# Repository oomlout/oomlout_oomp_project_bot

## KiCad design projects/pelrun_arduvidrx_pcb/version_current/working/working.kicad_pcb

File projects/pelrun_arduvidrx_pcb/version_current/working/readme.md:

# OOMP Project  
## arduvidrx_pcb  by pelrun  
  
oomp key: oomp_projects_flat_pelrun_arduvidrx_pcb  
(snippet of original readme)  

  full source readme at [readme_src.md](readme_src.md)  
  
source repo at: [https://github.com/pelrun/arduvidrx_pcb](https://github.com/pelrun/arduvidrx_pcb)  
## Board  

## Schematic  

[schematic pdf](working_schematic.pdf)  
## Images

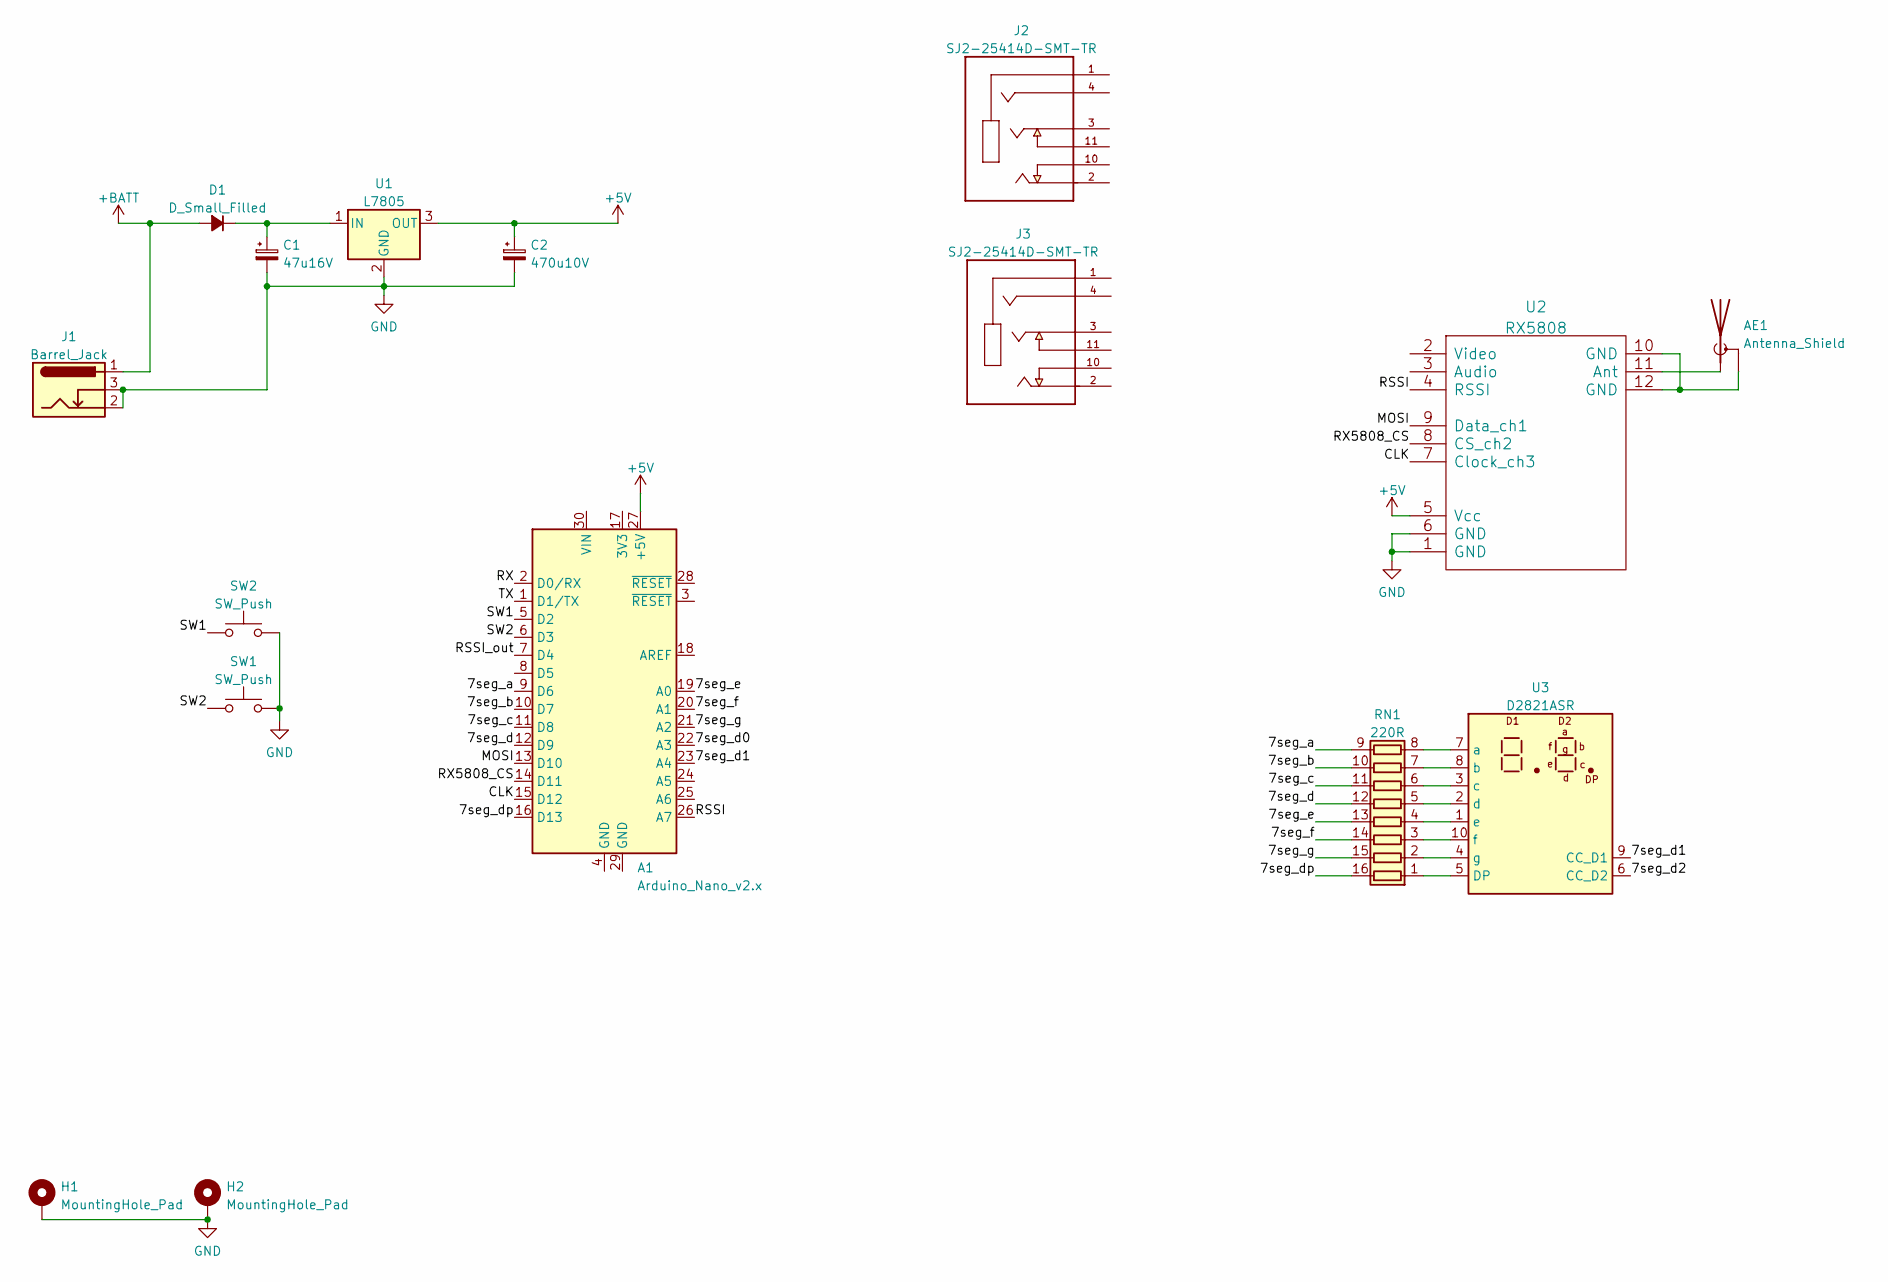
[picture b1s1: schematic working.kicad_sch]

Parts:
A1: Arduino_Nano_v2.x; Arduino_Nano
AE1: Antenna_Shield; SMA_Samtec_SMA-J-P-X-ST-EM1_EdgeMount
C1: 47u16V; CP_Radial_D4.0mm_P2.00mm
C2: 470u10V; CP_Radial_D4.0mm_P2.00mm
D1: D_Small_Filled; D_SMA-SMB_Universal_Handsoldering
H1, H2: MountingHole_Pad; MountingHole_3mm_Pad
J1: Barrel_Jack; PJ040CH
J2, J3: SJ2-25414D-SMT-TR; CUI_SJ2-25414D-SMT-TR; PARTREV 1.01
RN1: 220R; R_Array_Convex_8x0602
SW1, SW2: SW_Push; SW_PUSH_6mm_H13mm
U1: L7805; TO-252-2
U2: RX5808
U3: D2821ASR; HDSP-7401

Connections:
+5V: A1.27 (+5V), C2.1, U1.3 (OUT), U2.5 (Vcc)
+BATT: D1.2 (A), J1.1
/7seg_a: A1.9 (D6), RN1.9 (R8.2)
/7seg_b: A1.10 (D7), RN1.10 (R7.2)
/7seg_c: A1.11 (D8), RN1.11 (R6.2)
/7seg_d: A1.12 (D9), RN1.12 (R5.2)
/7seg_d0: A1.22 (A3)
/7seg_d1: A1.23 (A4), U3.9 (CC_D1)
/7seg_d2: U3.6 (CC_D2)
/7seg_dp: A1.16 (D13), RN1.16 (R1.2)
/7seg_e: A1.19 (A0), RN1.13 (R4.2)
/7seg_f: A1.20 (A1), RN1.14 (R3.2)
/7seg_g: A1.21 (A2), RN1.15 (R2.2)
/CLK: A1.15 (D12), U2.7 (Clock_ch3)
/MOSI: A1.13 (D10), U2.9 (Data_ch1)
/RSSI: A1.26 (A7), U2.4 (RSSI)
/RSSI_out: A1.7 (D4)
/RX: A1.2 (D0/RX)
/RX5808_CS: A1.14 (D11), U2.8 (CS_ch2)
/SW1: A1.5 (D2), SW2.1
/SW2: A1.6 (D3), SW1.1
/TX: A1.1 (D1/TX)
GND: C1.2, C2.2, H1.1, H2.1, J1.2, J1.3, SW1.2, SW2.2, U1.2 (GND), U2.1 (GND), U2.6 (GND)
unnamed: AE1.1 (A), U2.11 (Ant)
unnamed: AE1.2 (Shield), U2.10 (GND), U2.12 (GND)
unnamed: C1.1, D1.1 (K), U1.1 (IN)
unnamed: RN1.1 (R1.1), U3.5 (DP)
unnamed: RN1.2 (R2.1), U3.4 (g)
unnamed: RN1.3 (R3.1), U3.10 (f)
unnamed: RN1.4 (R4.1), U3.1 (e)
unnamed: RN1.5 (R5.1), U3.2 (d)
unnamed: RN1.6 (R6.1), U3.3 (c)
unnamed: RN1.7 (R7.1), U3.8 (b)
unnamed: RN1.8 (R8.1), U3.7 (a)

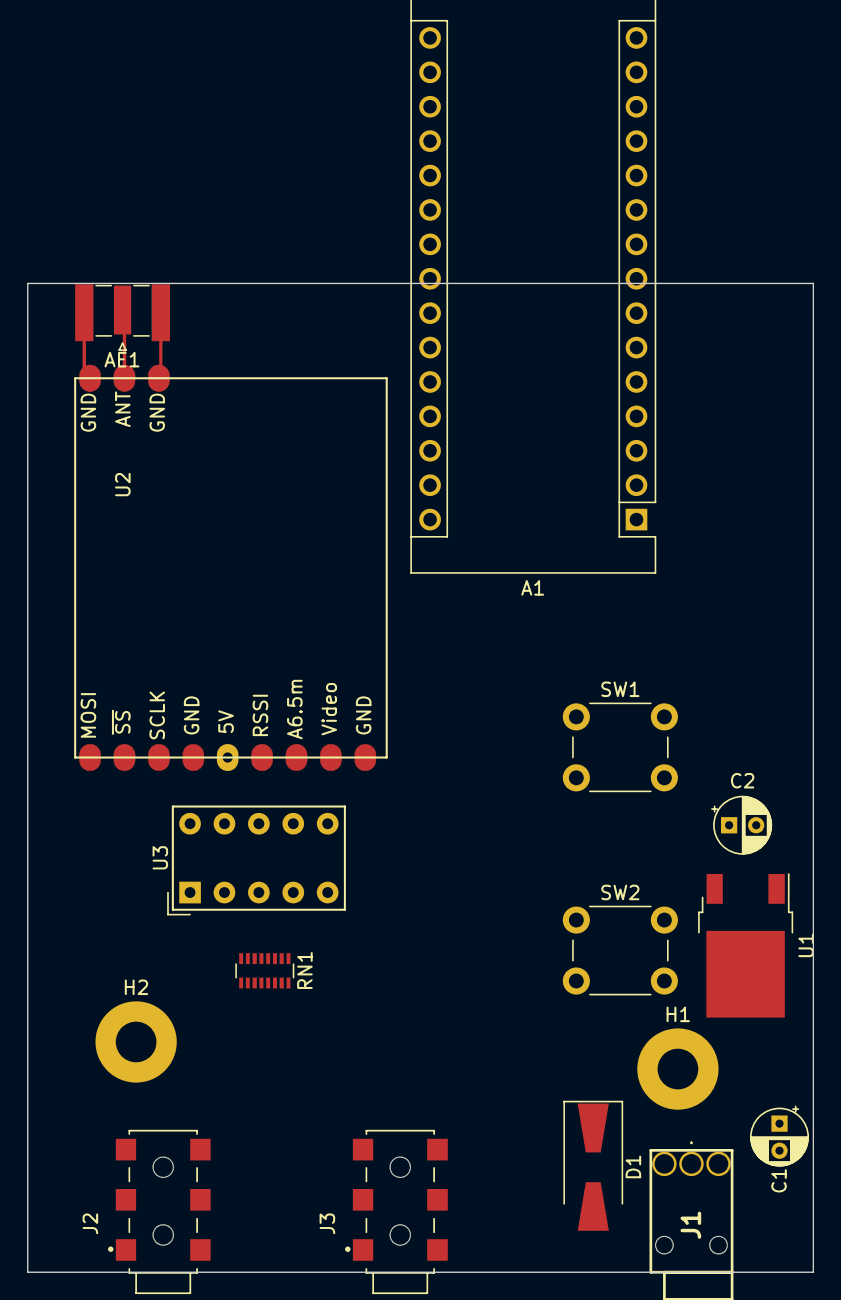
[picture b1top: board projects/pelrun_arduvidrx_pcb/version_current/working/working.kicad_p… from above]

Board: 2 copper layers, 58.0 x 73.0 mm, 16 parts (0 on the bottom side), 29 nets.

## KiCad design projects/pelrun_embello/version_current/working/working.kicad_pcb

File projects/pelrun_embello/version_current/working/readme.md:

# embello by pelrun  
This is a harvested standardized copy of a project from github.  
The original project can be found at:  
https://github.com/pelrun/embello  
Please consult that link for additional, details, files, and license information.  
Note: It was auto harvested and if the original repo had more than one board file or anything out of the ordinary the files here are likely not representative.

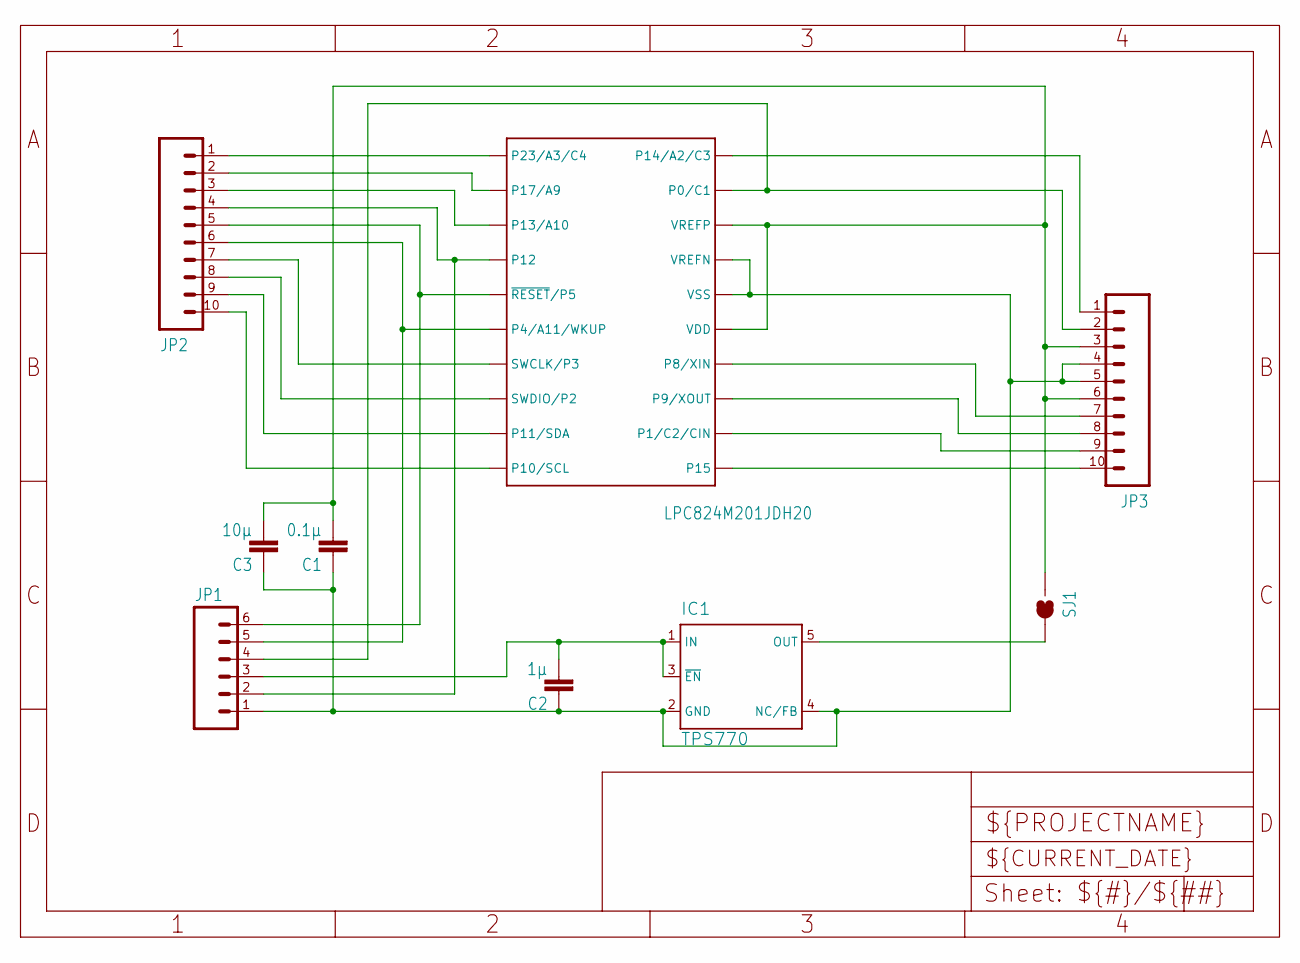
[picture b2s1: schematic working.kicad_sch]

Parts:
C1: 0.1µ; C0603K
C2: 1µ; C0603K
C3: 10µ; C0805K
IC1: TPS770; SOT23-DBV
JP1: M06LONGPADS; 1X06_LONGPADS
JP2, JP3: M10NO_SILK_PTH_FEMALE; 1X10_NO_SILK
SJ1: SOLDERJUMPERTRACE; SJ_2S-TRACE
U$3: LPC824M201JDH20; TSSOP20

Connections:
GND: C1.1, C2.1, C3.1, IC1.2 (GND), IC1.4 (NC/FB), JP1.1, JP3.4, JP3.5, U$3.16 (VSS), U$3.17 (VREFN)
unnamed: JP2.1, U$3.1 (P23/A3/C4)
unnamed: C2.2, IC1.1 (IN), IC1.3 (~EN), JP1.3
unnamed: JP1.4, JP3.2, U$3.19 (P0/C1)
unnamed: C1.2, C3.2, JP3.3, JP3.6, SJ1.1, U$3.15 (VDD), U$3.18 (VREFP)
unnamed: JP1.5, JP2.6, U$3.6 (P4/A11/WKUP)
unnamed: JP2.2, U$3.2 (P17/A9)
unnamed: JP3.1, U$3.20 (P14/A2/C3)
unnamed: JP3.7, U$3.14 (P8/XIN)
unnamed: JP3.8, U$3.13 (P9/XOUT)
unnamed: JP3.9, U$3.12 (P1/C2/CIN)
unnamed: JP3.10, U$3.11 (P15)
unnamed: JP1.2, JP2.4, U$3.4 (P12)
unnamed: JP2.3, U$3.3 (P13/A10)
unnamed: JP1.6, JP2.5, U$3.5 (~RESET/P5)
unnamed: IC1.5 (OUT), SJ1.2
unnamed: JP2.7, U$3.7 (SWCLK/P3)
unnamed: JP2.8, U$3.8 (SWDIO/P2)
unnamed: JP2.9, U$3.9 (P11/SDA)
unnamed: JP2.10, U$3.10 (P10/SCL)

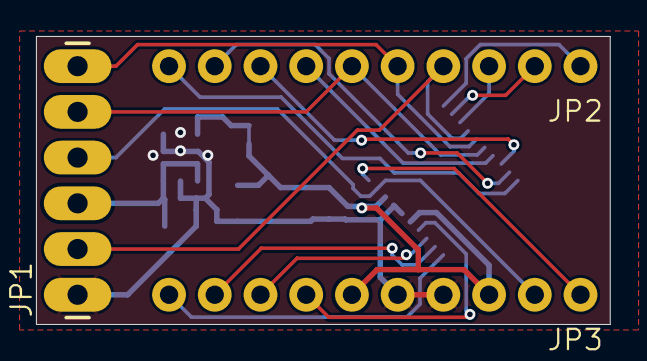
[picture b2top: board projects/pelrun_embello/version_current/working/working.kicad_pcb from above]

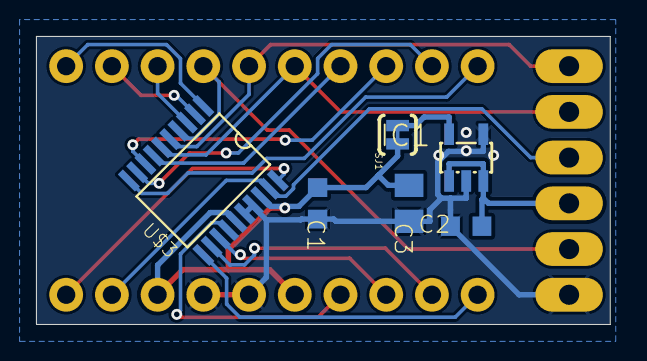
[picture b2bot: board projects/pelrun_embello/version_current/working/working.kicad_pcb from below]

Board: 2 copper layers, 31.9 x 16.0 mm, 9 parts (6 on the bottom side), 20 nets.

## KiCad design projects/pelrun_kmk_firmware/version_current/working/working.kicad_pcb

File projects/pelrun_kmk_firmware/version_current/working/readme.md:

# kmk_firmware by pelrun  
This is a harvested standardized copy of a project from github.  
The original project can be found at:  
https://github.com/pelrun/kmk_firmware  
Please consult that link for additional, details, files, and license information.  
Note: It was auto harvested and if the original repo had more than one board file or anything out of the ordinary the files here are likely not representative.

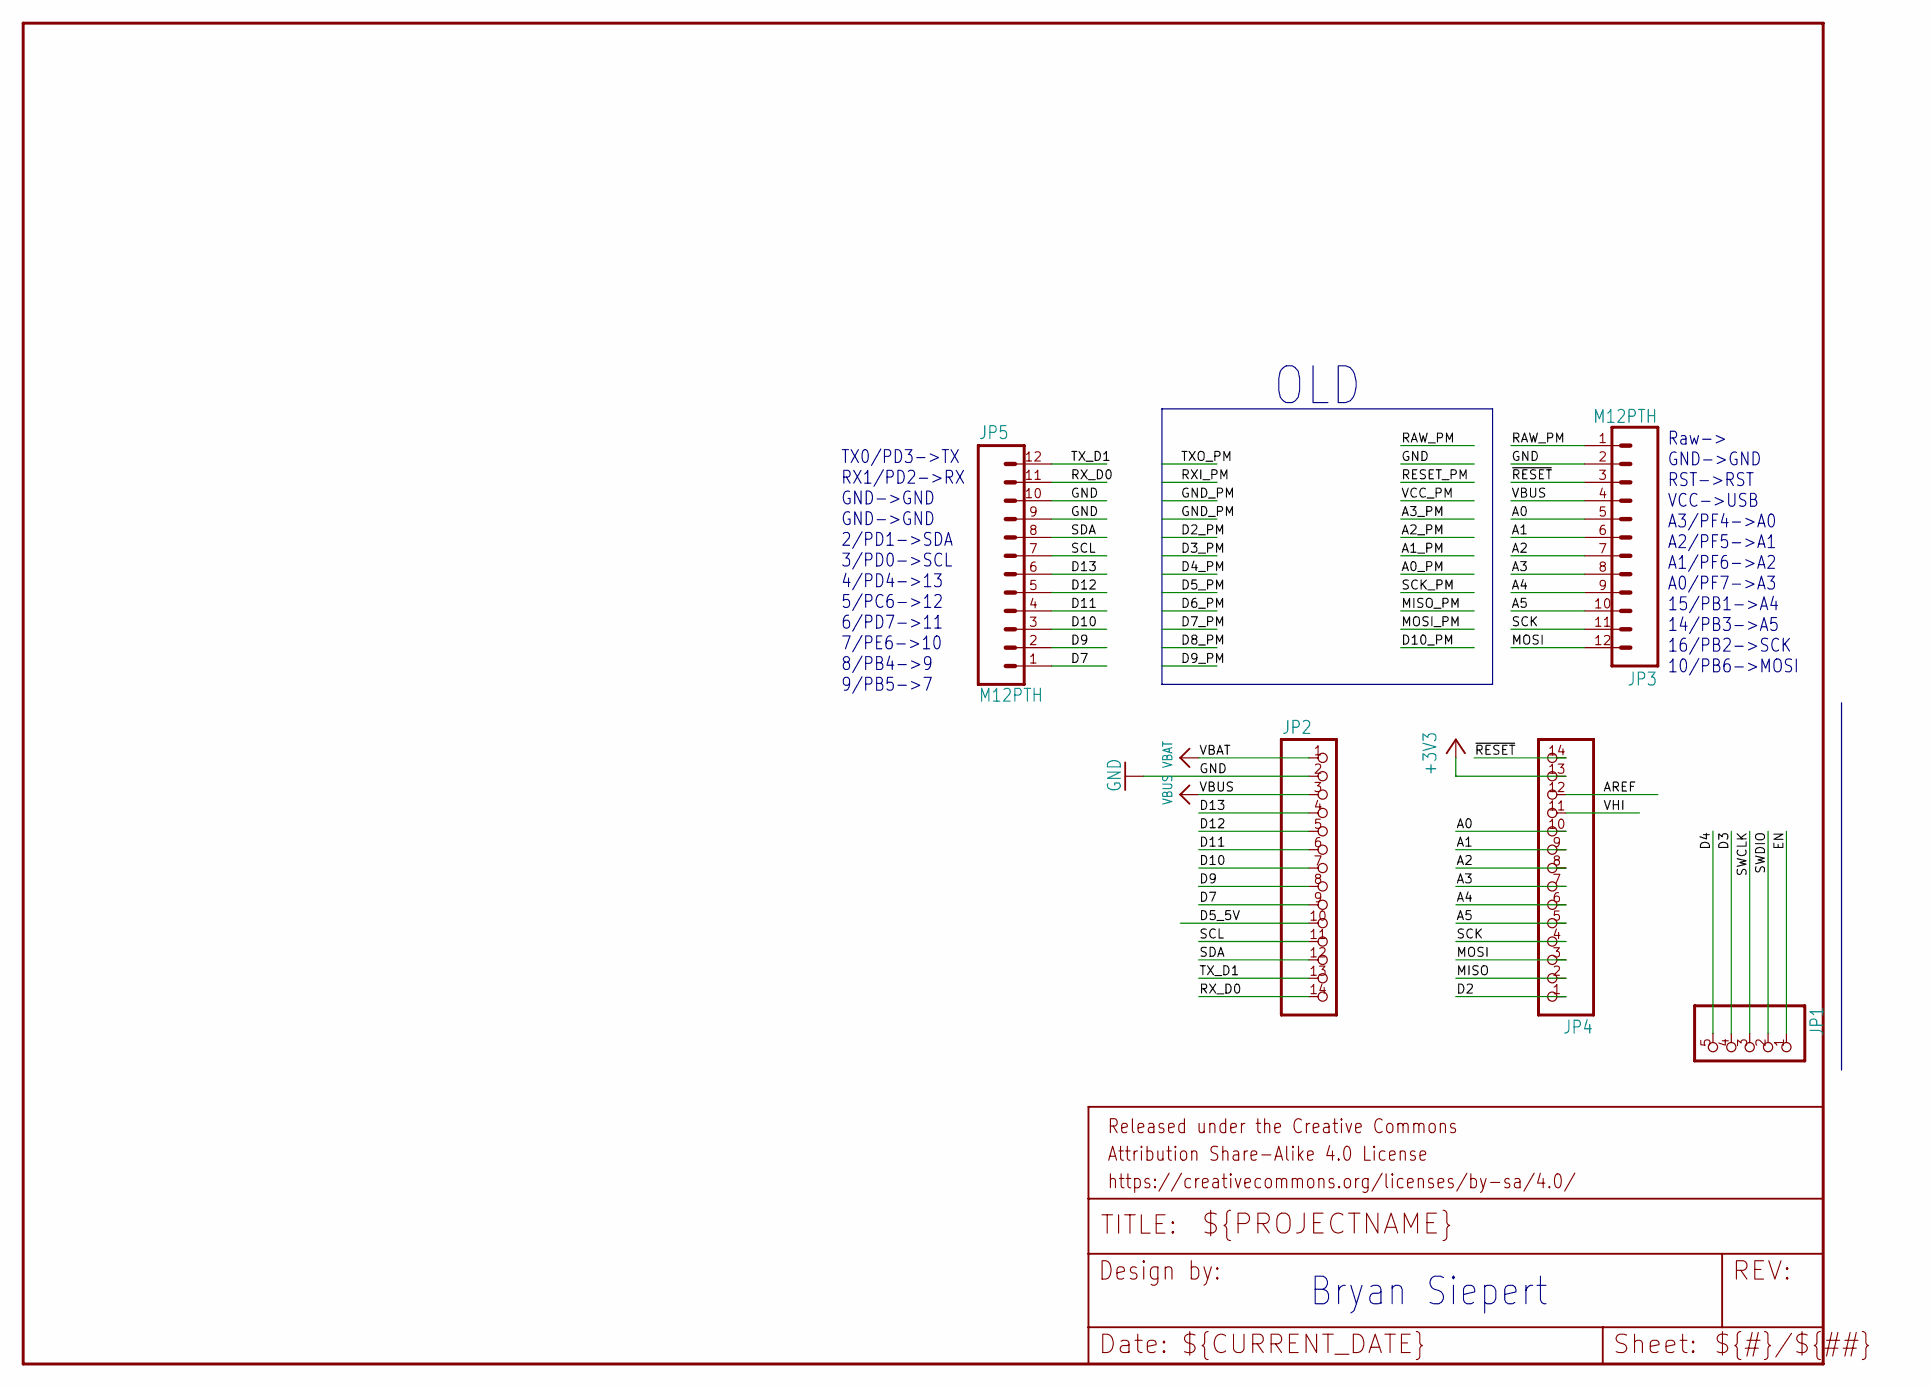
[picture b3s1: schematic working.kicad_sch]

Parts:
FRAME2: FRAME-LETTER; CREATIVE_COMMONS
JP1: HEADER-1X570MIL; 1X05_ROUND_70
JP2, JP4: HEADER-1X14; 1X14_ROUND70
JP3, JP5: M12PTH; 1X12

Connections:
+3V3: JP4.13
A0: JP3.5, JP4.10
A1: JP3.6, JP4.9
A2: JP3.7, JP4.8
A3: JP3.8, JP4.7
A4: JP3.9, JP4.6
A5: JP3.10, JP4.5
AREF: JP4.12
D2: JP4.1
D3: JP1.4
D4: JP1.5
D5_5V: JP2.10
D7: JP2.9, JP5.1
D9: JP2.8, JP5.2
D10: JP2.7, JP5.3
D11: JP2.6, JP5.4
D12: JP2.5, JP5.5
D13: JP2.4, JP5.6
EN: JP1.1
GND: JP2.2, JP3.2, JP5.9, JP5.10
MISO: JP4.2
MOSI: JP3.12, JP4.3
RAW_PM: JP3.1
RX_D0: JP2.14, JP5.11
SCK: JP3.11, JP4.4
SCL: JP2.11, JP5.7
SDA: JP2.12, JP5.8
SWCLK: JP1.3
SWDIO: JP1.2
TX_D1: JP2.13, JP5.12
VBAT: JP2.1
VBUS: JP2.3, JP3.4
VHI: JP4.11
~RESET: JP3.3, JP4.14

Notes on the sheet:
Bryan Siepert
Raw-> GND->GND RST->RST VCC->USB A3/PF4->A0 A2/PF5->A1 A1/PF6->A2 A0/PF7->A3 15/PB1->A4 14/PB3->A5 16/PB2->SCK 10/PB6->MOSI
TX0/PD3->TX RX1/PD2->RX GND->GND GND->GND 2/PD1->SDA 3/PD0->SCL 4/PD4->13 5/PC6->12 6/PD7->11 7/PE6->10 8/PB4->9 9/PB5->7
OLD

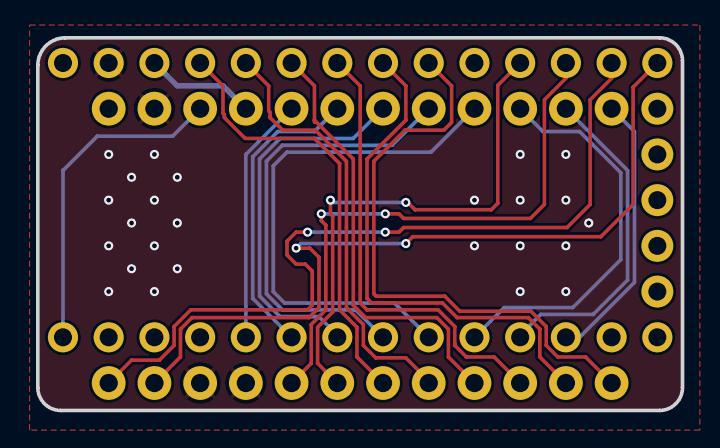
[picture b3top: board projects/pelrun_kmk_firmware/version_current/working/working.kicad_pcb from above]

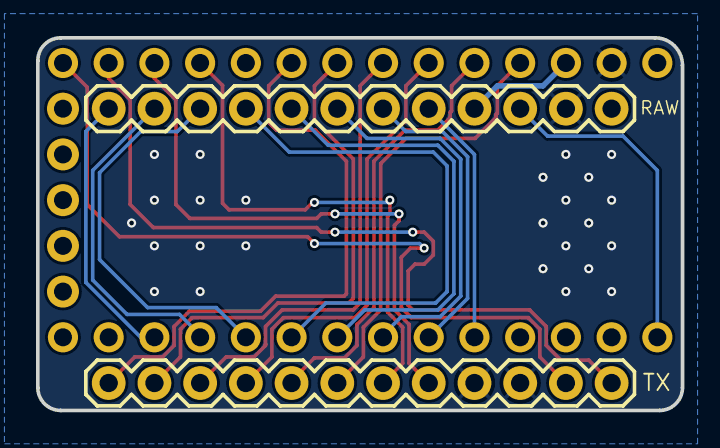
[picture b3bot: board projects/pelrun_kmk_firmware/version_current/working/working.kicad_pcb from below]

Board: 4 copper layers, 35.8 x 20.7 mm, 6 parts (2 on the bottom side), 21 nets.

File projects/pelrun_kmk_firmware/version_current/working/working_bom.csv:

"Id";"Designator";"Footprint";"Quantity";"Designation";"Supplier and ref";
1;"JP2,JP4";"1X14_ROUND70";2;"";;;
2;"FRAME2";"CREATIVE_COMMONS";1;"FRAME-LETTER";;;
3;"JP1";"1X05_ROUND_70";1;"";;;
4;"JP5,JP3";"1X12";2;"";;;

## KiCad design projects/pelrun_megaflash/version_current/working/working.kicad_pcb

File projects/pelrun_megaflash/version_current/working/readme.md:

# OOMP Project  
## megaflash  by pelrun  
  
oomp key: oomp_projects_flat_pelrun_megaflash  
(snippet of original readme)  

  full source readme at [readme_src.md](readme_src.md)  
  
source repo at: [https://github.com/pelrun/megaflash](https://github.com/pelrun/megaflash)  
## Board  

## Schematic  

[schematic pdf](working_schematic.pdf)  
## Images

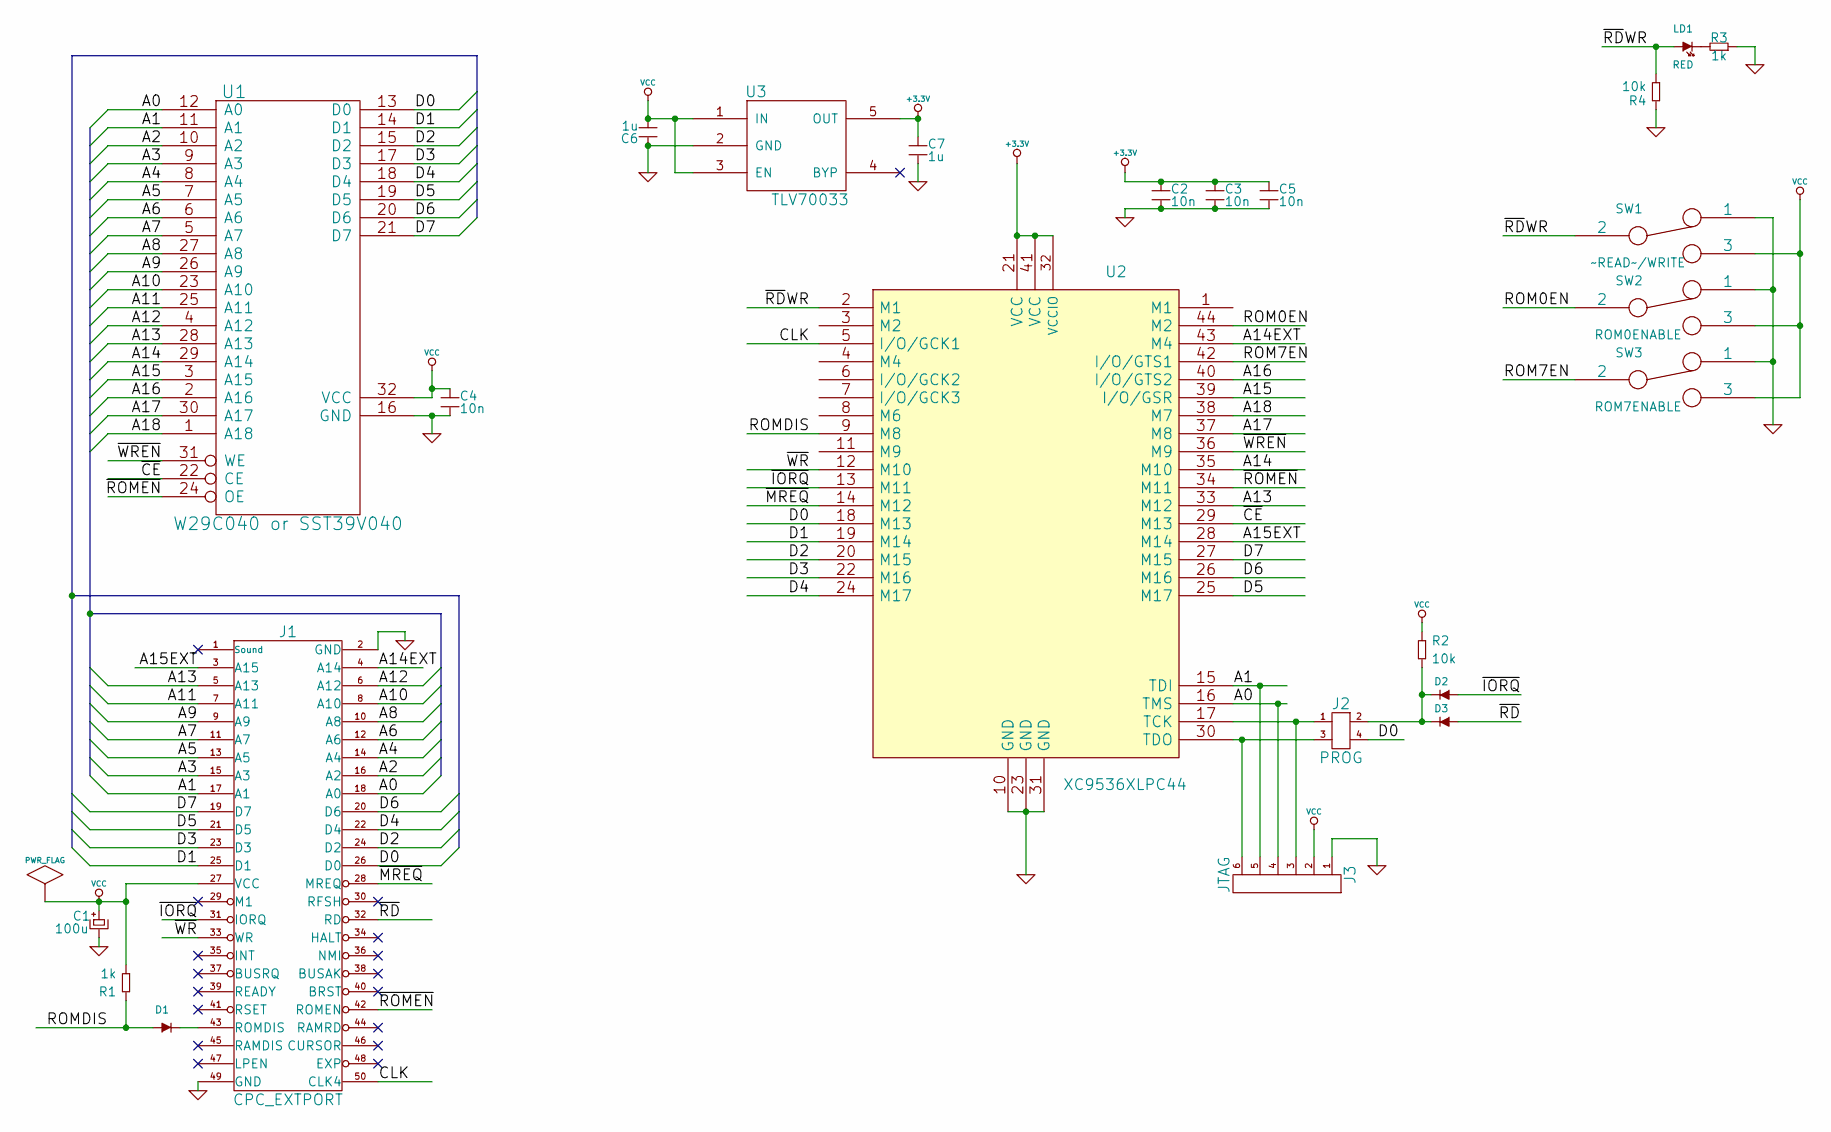
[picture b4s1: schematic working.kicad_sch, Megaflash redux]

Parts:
C1: 100u
C2, C3, C4, C5: 10n
C6, C7: 1u
D1, D2, D3: DIODE
J1: CPC_EXTPORT
J2: PROG
J3: JTAG
LD1: RED
R1, R3: 1k
R2, R4: 10k
SW1: ~READ~/WRITE
SW2: ROM0ENABLE
SW3: ROM7ENABLE
U1: W29C040 or SST39V040
U2: XC9536XLPC44
U3: TLV70033

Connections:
+3.3V: C2.1, C3.1, C5.1, C7.1, U2.21 (VCC), U2.32 (VCCIO), U2.41 (VCC), U3.5 (OUT)
/A0: J1.18 (A0), J3.4, U1.12 (A0), U2.16 (TMS)
/A1: J1.17 (A1), J3.5, U1.11 (A1), U2.15 (TDI)
/A2: J1.16 (A2), U1.10 (A2)
/A3: J1.15 (A3), U1.9 (A3)
/A4: J1.14 (A4), U1.8 (A4)
/A5: J1.13 (A5), U1.7 (A5)
/A6: J1.12 (A6), U1.6 (A6)
/A7: J1.11 (A7), U1.5 (A7)
/A8: J1.10 (A8), U1.27 (A8)
/A9: J1.9 (A9), U1.26 (A9)
/A10: J1.8 (A10), U1.23 (A10)
/A11: J1.7 (A11), U1.25 (A11)
/A12: J1.6 (A12), U1.4 (A12)
/A13: J1.5 (A13), U1.28 (A13), U2.33 (M12)
/A14: U1.29 (A14), U2.35 (M10)
/A14EXT: J1.4 (A14), U2.43 (M4)
/A15: U1.3 (A15), U2.39 (I/O/GSR)
/A15EXT: J1.3 (A15), U2.28 (M14)
/A16: U1.2 (A16), U2.40 (I/O/GTS2)
/A17: U1.30 (A17), U2.37 (M8)
/A18: U1.1 (A18), U2.38 (M7)
/CLK: J1.50 (CLK4), U2.5 (I/O/GCK1)
/D0: J1.26 (D0), J2.4, U1.13 (D0), U2.18 (M13)
/D1: J1.25 (D1), U1.14 (D1), U2.19 (M14)
/D2: J1.24 (D2), U1.15 (D2), U2.20 (M15)
/D3: J1.23 (D3), U1.17 (D3), U2.22 (M16)
/D4: J1.22 (D4), U1.18 (D4), U2.24 (M17)
/D5: J1.21 (D5), U1.19 (D5), U2.25 (M17)
/D6: J1.20 (D6), U1.20 (D6), U2.26 (M16)
/D7: J1.19 (D7), U1.21 (D7), U2.27 (M15)
/ROM0EN: SW2.2, U2.44 (M2)
/ROM7EN: SW3.2, U2.42 (I/O/GTS1)
/ROMDIS: D1.1 (A), R1.2, U2.9 (M8)
/~CE: U1.22 (CE), U2.29 (M13)
/~IORQ: D2.1 (A), J1.31 (IORQ), U2.13 (M11)
/~MREQ: J1.28 (MREQ), U2.14 (M12)
/~RD: D3.1 (A), J1.32 (RD)
/~RD~WR: LD1.1 (A), R4.1, SW1.2, U2.2 (M1)
/~ROMEN: J1.42 (ROMEN), U1.24 (OE), U2.34 (M11)
/~WR: J1.33 (WR), U2.12 (M10)
/~WREN: U1.31 (WE), U2.36 (M9)
GND: C1.2, C2.2, C3.2, C4.2, C5.2, C6.1, C7.2, J1.2 (GND), J1.49 (GND), J3.1, R3.1, R4.2, SW1.1, SW2.1, SW3.1, U1.16 (GND), U2.10 (GND), U2.23 (GND), U2.31 (GND), U3.2 (GND)
unnamed: D1.2 (K), J1.43 (ROMDIS)
unnamed: D2.2 (K), D3.2 (K), J2.2, R2.2
unnamed: J2.1, J3.3, U2.17 (TCK)
unnamed: J2.3, J3.6, U2.30 (TDO)
unnamed: LD1.2 (K), R3.2
VCC: C1.1, C4.1, C6.2, J1.27 (VCC), J3.2, R1.1, R2.1, SW1.3, SW2.3, SW3.3, U1.32 (VCC), U3.1 (IN), U3.3 (EN)

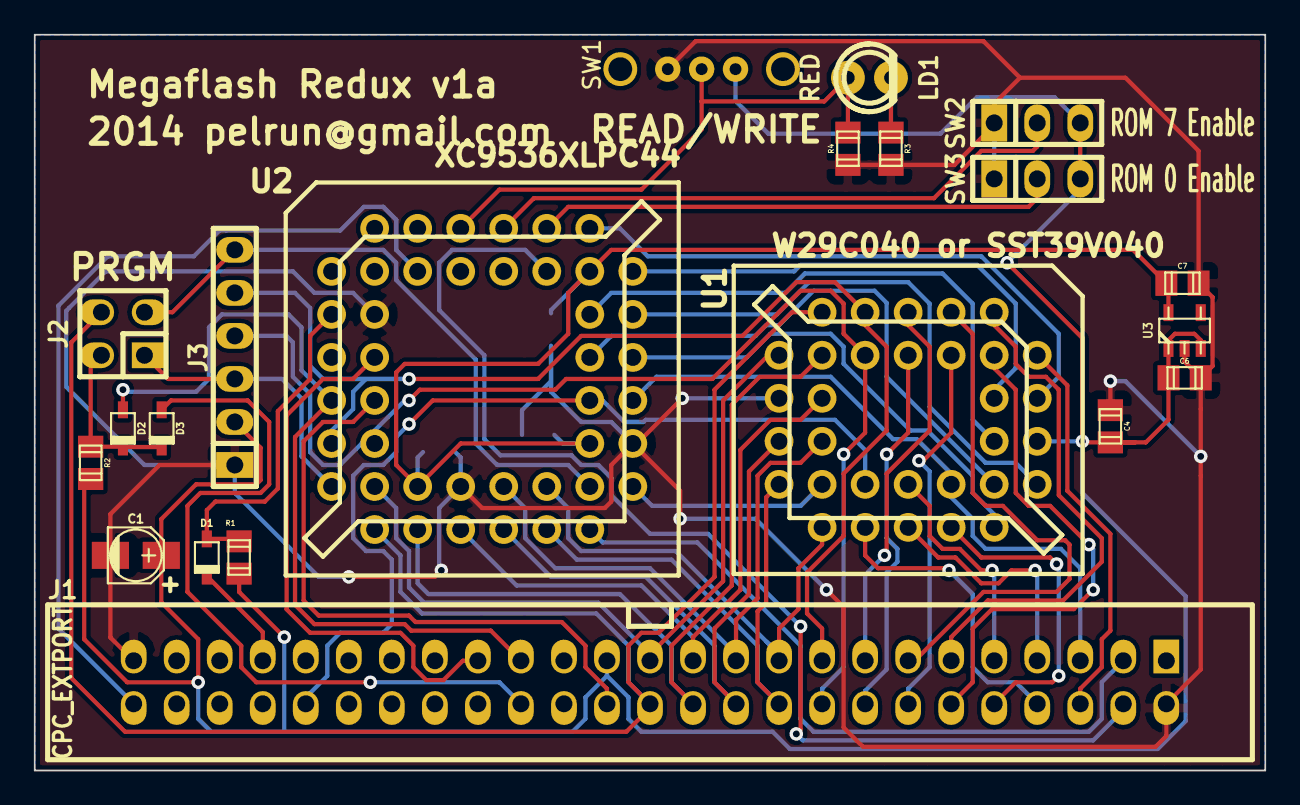
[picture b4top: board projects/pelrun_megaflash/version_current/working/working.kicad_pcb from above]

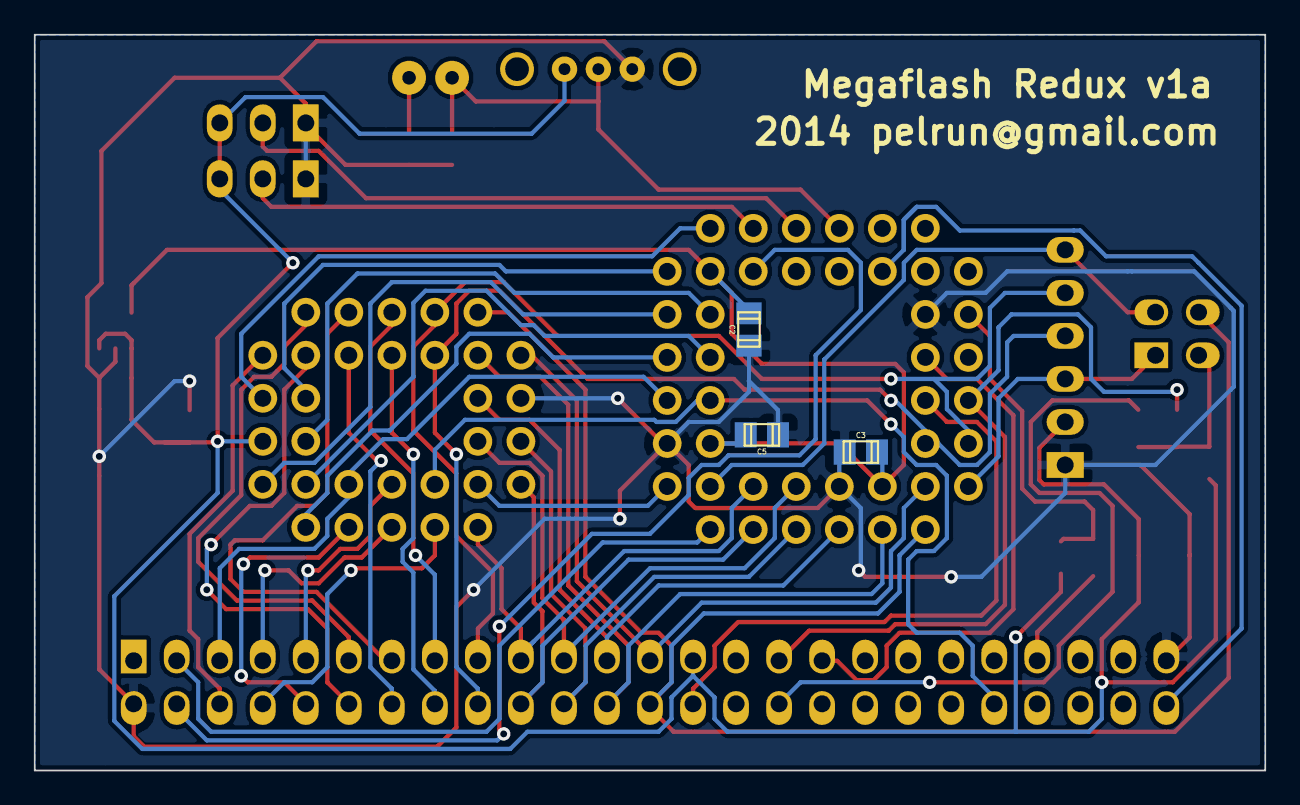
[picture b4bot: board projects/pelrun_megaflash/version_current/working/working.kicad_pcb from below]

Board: 2 copper layers, 72.6 x 43.4 mm, 24 parts (3 on the bottom side), 49 nets.

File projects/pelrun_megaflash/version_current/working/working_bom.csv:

"Id";"Designator";"Footprint";"Quantity";"Designation";"Supplier and ref";
1;"C1";"c_elec_3x5.3";1;"100u";;;
2;"C2,C3,C4,C5";"c_0805";4;"10n";;;
3;"J1";"vasch_strip_25x2";1;"CPC_EXTPORT";;;
4;"R1,R3";"r_0805";2;"1k";;;
5;"U1";"plcc32_pth-skt";1;"W29C040 or SST39V040";;;
6;"D1,D2,D3";"sod323";3;"DIODE";;;
7;"SW2";"pin_strip_3";1;"ROM0ENABLE";;;
8;"SW3";"pin_strip_3";1;"ROM7ENABLE";;;
9;"U2";"plcc44_pth-skt";1;"XC9536XLPC44";;;
10;"J2";"pin_strip_2x2";1;"PROG";;;
11;"R2,R4";"r_0805";2;"10k";;;
12;"LD1";"led_3mm_red";1;"RED";;;
13;"J3";"pin_strip_6";1;"JTAG";;;
14;"SW1";"switch-eg1213-spdt";1;"~{READ}/WRITE";;;
15;"C6,C7";"c_0805";2;"1u";;;
16;"U3";"sot23-5";1;"TLV70033";;;

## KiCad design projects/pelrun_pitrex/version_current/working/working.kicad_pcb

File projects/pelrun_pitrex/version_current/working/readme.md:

# OOMP Project  
## piTrex  by pelrun  
  
oomp key: oomp_projects_flat_pelrun_pitrex  
(snippet of original readme)  

  full source readme at [readme_src.md](readme_src.md)  
  
source repo at: [https://github.com/pelrun/piTrex](https://github.com/pelrun/piTrex)  
## Board  

## Schematic  

[schematic pdf](working_schematic.pdf)  
## Images

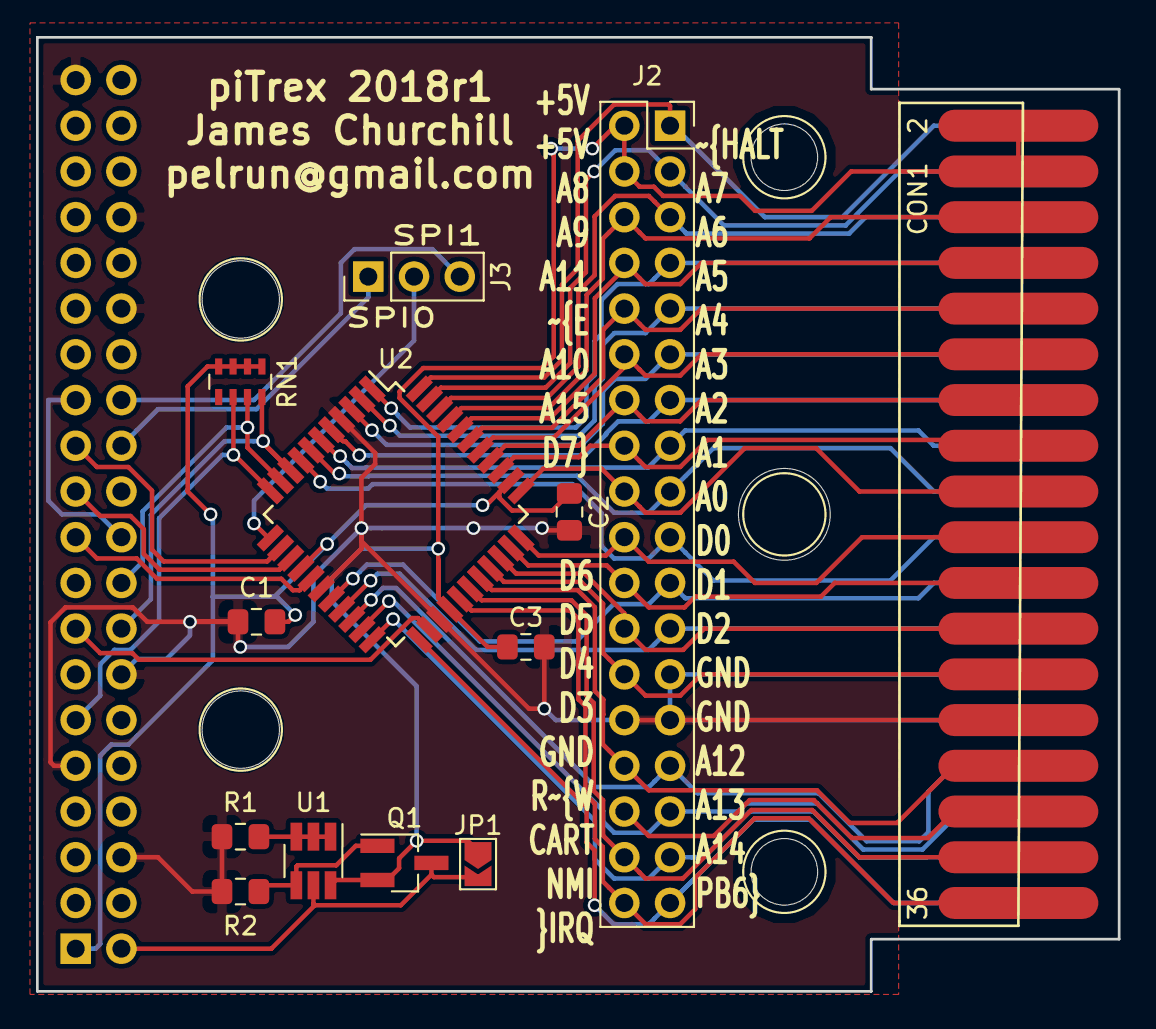
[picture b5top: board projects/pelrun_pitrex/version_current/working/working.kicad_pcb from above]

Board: 2 copper layers, 60.1 x 53.0 mm, 19 parts (1 on the bottom side), 47 nets.

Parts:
C1, C2, C3: 0.1u; C_0805_2012Metric_Pad1.15x1.40mm_HandSolder
CON1: vectrex-edge-connector; vectrex
J1: Raspberry_Pi_2_3; PiZeroHat
J2: Test; PinSocket_2x18_P2.54mm_Vertical
J3: SPI Sel; PinHeader_1x03_P2.54mm_Vertical
JP1: bypass; SolderJumper-2_P1.3mm_Open_TrianglePad1.0x1.5mm
Q1: DMG2305UX; SOT-23_Handsoldering
R1, R2: 10k; R_0805_2012Metric_Pad1.15x1.40mm_HandSolder
RN1: 47k; R_Array_Concave_4x0603
U1: DMMT5401; SOT-23-6_Handsoldering
U2: XC9572XL-VQFP44; LQFP-44_10x10mm_P0.8mm
hole1, hole2, hole3, hole4, hole5: 1pin

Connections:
+3V3: C1.1, C2.1, J1.1, RN1.1, RN1.2, RN1.3, RN1.4, U2.15, U2.35
+5V: C3.1, CON1.2, CON1.4, J2.2, J2.4, Q1.2, U1.6, U2.26
/A0: CON1.17, J2.17, U2.7
/A1: CON1.15, J2.15, U2.6
/A2: CON1.13, J2.13, U2.5
/A3: CON1.11, J2.11, U2.3
/A4: CON1.9, J2.9, U2.2
/A5: CON1.7, J2.7, U2.1
/A6: CON1.5, J2.5, U2.42
/A7: CON1.3, J2.3, U2.43
/A8: CON1.6, J2.6, U2.41
/A9: CON1.8, J2.8, U2.40
/A10: CON1.14, J2.14, U2.37
/A11: CON1.10, J2.10, U2.39
/A12: CON1.29, J2.29, U2.20
/A13: CON1.31, J2.31, U2.21
/A14: CON1.33, J2.33, U2.22
/A15: CON1.16, J2.16, U2.36
/CART: CON1.32, J2.32
/D0: CON1.19, J2.19, U2.8
/D1: CON1.21, J2.21, U2.18
/D2: CON1.23, J2.23, U2.19
/D3: CON1.26, J2.26, U2.30
/D4: CON1.24, J2.24, U2.31
/D5: CON1.22, J2.22, U2.32
/D6: CON1.20, J2.20, U2.33
/D7: CON1.18, J2.18, U2.34
/JTAG_TCK: J1.11, RN1.6, U2.11
/JTAG_TDI: J1.16, RN1.8, U2.9
/JTAG_TDO: J1.15, U2.24
/JTAG_TMS: J1.18, RN1.7, U2.10
/NMI: CON1.34, J2.34, U2.28
/R/~W: CON1.30, J2.30, U2.29
/SPI_MISO: J1.21, U2.14
/SPI_MOSI: J1.19, U2.16
/SPI_SCK: J1.23, U2.13
/VIA_PB6: CON1.35, J2.35, U2.23
/~E: CON1.12, J2.12, U2.38
/~HALT: CON1.1, J2.1, U2.44
/~IRQ: CON1.36, J2.36, U2.27
/~SPI_CE: J3.2, U2.12
/~SPI_CE0: J1.24, J3.1
/~SPI_CE1: J1.26, J3.3
GND: C1.2, C2.2, C3.2, CON1.25, CON1.27, CON1.28, J1.6, J1.9, J1.14, J1.20, J1.25, J1.30, J1.34, J1.39, J2.25, J2.27, J2.28, R1.2, R2.2, U2.4, U2.17, U2.25
unnamed: Q1.1, R2.1, U1.4
unnamed: R1.1, U1.1, U1.2, U1.3
VCC: J1.2, Q1.3, U1.5

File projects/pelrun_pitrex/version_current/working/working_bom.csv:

"Id";"Designator";"Footprint";"Quantity";"Designation";"Supplier and ref";
1;"U2";"LQFP-44_10x10mm_P0.8mm";1;"XC9572XL-VQFP44";;;
2;"hole4,hole5,hole3,hole1,hole2";"1pin";5;"1pin";;;
3;"C1,C2,C3";"C_0805_2012Metric_Pad1.15x1.40mm_HandSolder";3;"0.1u";;;
4;"J2";"PinSocket_2x18_P2.54mm_Vertical";1;"Test";;;
5;"Q1";"SOT-23_Handsoldering";1;"DMG2305UX";;;
6;"R1,R2";"R_0805_2012Metric_Pad1.15x1.40mm_HandSolder";2;"10k";;;
7;"RN1";"R_Array_Concave_4x0603";1;"47k";;;
8;"U1";"SOT-23-6_Handsoldering";1;"DMMT5401";;;
9;"J3";"PinHeader_1x03_P2.54mm_Vertical";1;"SPI Sel";;;
10;"CON1";"vectrex";1;"vectrex-edge-connector";;;
11;"J1";"PiZeroHat";1;"Raspberry_Pi_2_3";;;

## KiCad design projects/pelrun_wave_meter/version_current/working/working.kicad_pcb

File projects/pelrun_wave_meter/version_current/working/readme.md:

# Wave_meter by pelrun  
This is a harvested standardized copy of a project from github.  
The original project can be found at:  
https://github.com/pelrun/Wave_meter  
Please consult that link for additional, details, files, and license information.  
Note: It was auto harvested and if the original repo had more than one board file or anything out of the ordinary the files here are likely not representative.

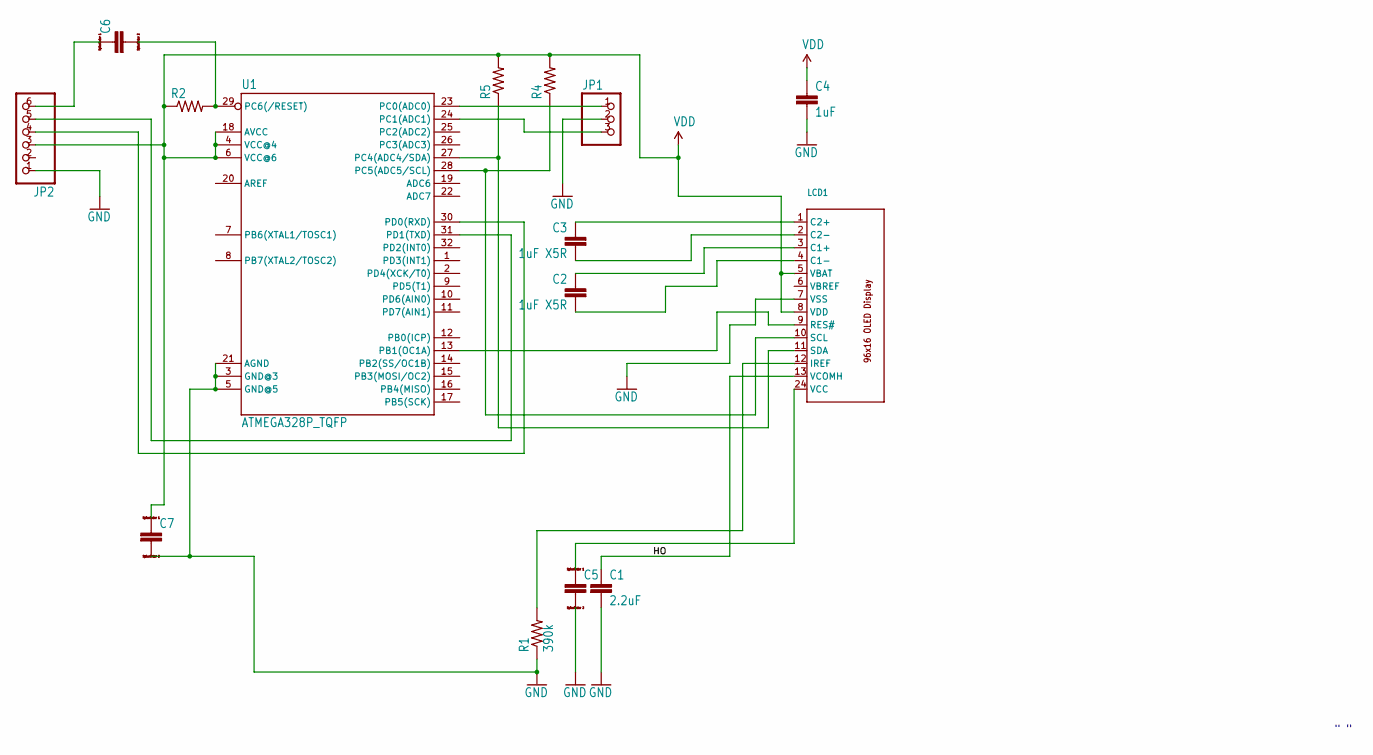
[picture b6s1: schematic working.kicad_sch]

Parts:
C1: 2.2uF; 0805
C2, C3: 1uF X5R; 0805
C4: 1uF; 0603-CAP
C5, C6, C7: CC0603; C0603
JP1: HEADER-1X3; 1X03_OVAL
JP2: HEADER-1X6; 1X06_OVAL
LCD1: DISP_OLED_UG-9616GLBBG02; UG-9616GLBBG02_0.65MM_WRAPAROUND
R1: 390k; 0603-RES
R2, R4, R5: R-US_R0603; R0603
U1: ATMEGA328P_TQFP; TQFP32-08

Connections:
C1N: C2.2, LCD1.4 (C1-)
C1P: C2.1, LCD1.3 (C1+)
C2N: C3.2, LCD1.2 (C2-)
C2P: C3.1, LCD1.1 (C2+)
GND: C1.2, C4.2, C5.2, C7.2, JP1.2, JP2.1, LCD1.7 (VSS), R1.1, U1.3 (GND@3), U1.5 (GND@5), U1.21 (AGND)
HO: C1.1, LCD1.13 (VCOMH)
IREF: LCD1.12 (IREF), R1.2
unnamed: LCD1.11 (SDA), R5.1, U1.27 (PC4(ADC4/SDA))
unnamed: C6.2, R2.2, U1.29 (PC6(/RESET))
unnamed: LCD1.9 (RES#), U1.13 (PB1(OC1A))
unnamed: C6.1, JP2.6
unnamed: JP1.1, U1.23 (PC0(ADC0))
unnamed: LCD1.10 (SCL), R4.1, U1.28 (PC5(ADC5/SCL))
unnamed: JP1.3, U1.24 (PC1(ADC1))
unnamed: JP2.5, U1.31 (PD1(TXD))
unnamed: JP2.4, U1.30 (PD0(RXD))
VCOMH: C5.1, LCD1.24 (VCC)
VDD: C4.1, C7.1, JP2.3, LCD1.5 (VBAT), LCD1.8 (VDD), R2.1, R4.2, R5.2, U1.4 (VCC@4), U1.6 (VCC@6), U1.18 (AVCC)

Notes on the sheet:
" "

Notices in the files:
projects/pelrun_kmk_firmware/version_current/working/working.kicad_sch:
https://creativecommons.org/licenses/by-sa/4.0
Released under the Creative Commons
parts and their libraries:
Released under the Creative Commons Attribution Share-Alike 4.0 License
